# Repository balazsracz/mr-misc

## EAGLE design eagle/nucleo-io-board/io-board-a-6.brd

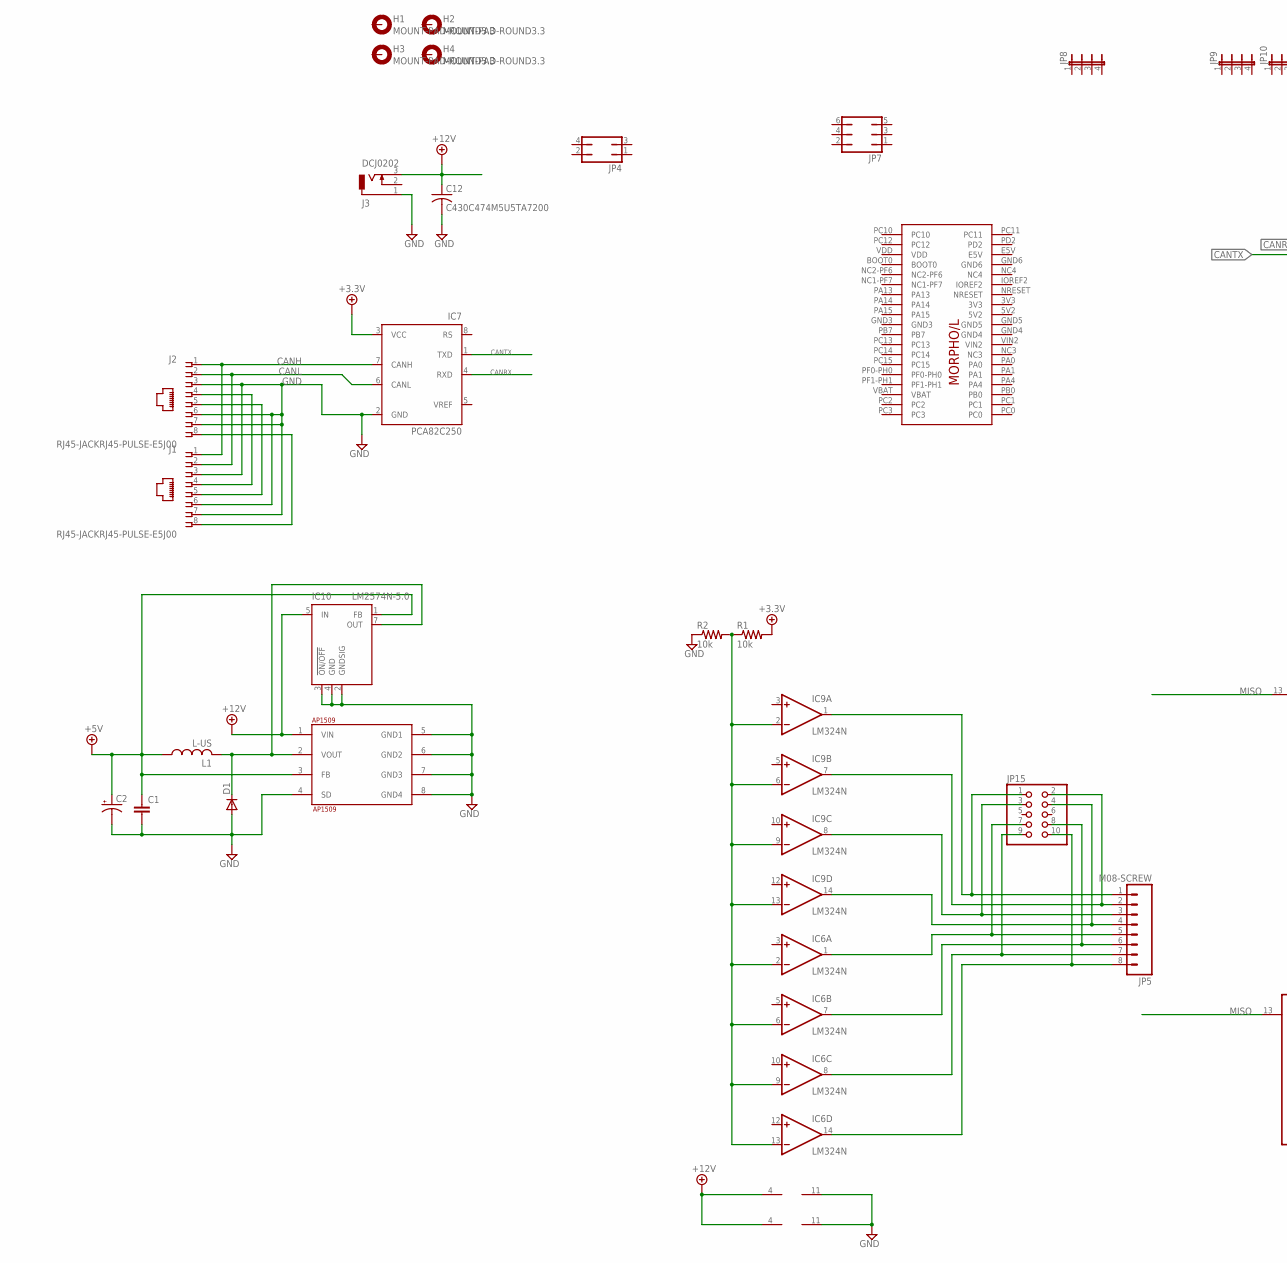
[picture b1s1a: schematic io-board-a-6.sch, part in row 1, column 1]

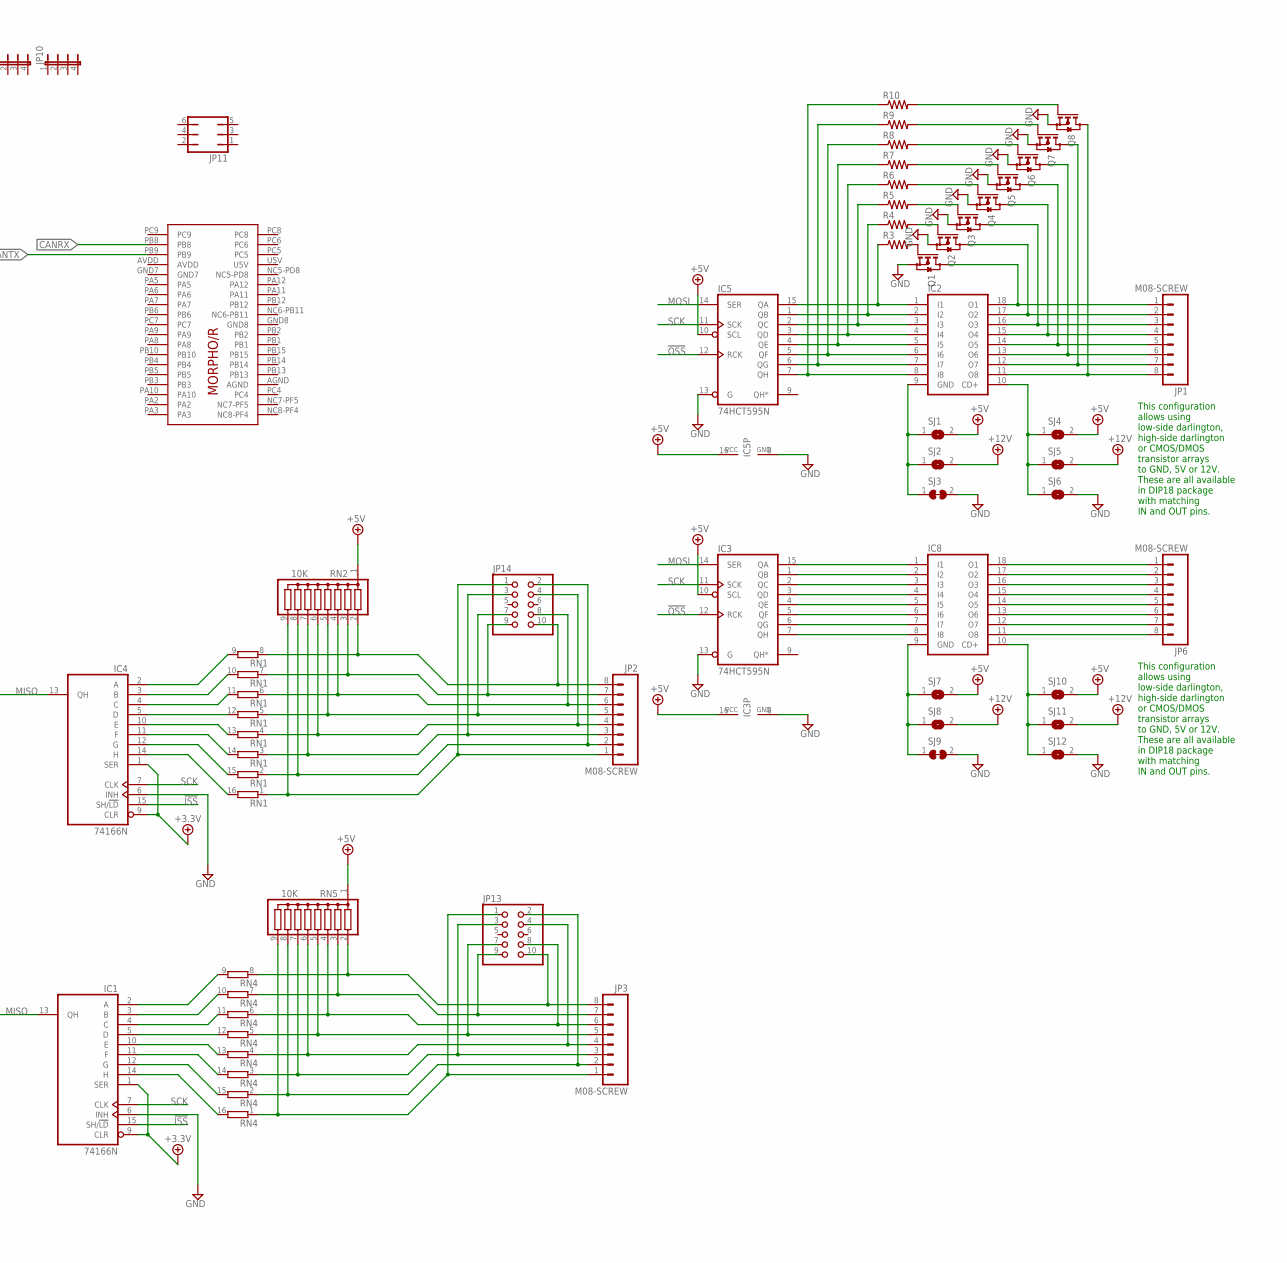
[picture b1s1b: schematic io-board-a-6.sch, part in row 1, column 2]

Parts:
+12V: 9-15V; POWER_USAGE
AP1509: AP1509; SO-08
C1: C-EUC1206; C1206
C2: CPOL-USE2.5-5; E2,5-5
C12: C430C474M5U5TA7200; C075-032X103
D1: DIODE-DO41-7.6; DO41-7.6
H1, H2, H3, H4: MOUNT-PAD-ROUND3.3; 3,3-PAD
IC1, IC4: 74166N; DIL16
IC2, IC8: ULN2803A; DIL18-THIN
IC3, IC5: 74HCT595N; DIL16
IC6, IC9: LM324N; DIL14
IC7: PCA82C250; DIL08
IC10: LM2574N-5.0; DIL08
J1, J2: RJ45-JACKRJ45-PULSE-E5J00; RJ45-PULSE-E5J88
J3: DCJ0202
JP1, JP2, JP3, JP5, JP6: M08-SCREW; 1X08_TERMINAL
JP4: JP2Q
JP7, JP11: JP3Q
JP8, JP9, JP10: JP4-FLAT; JP4F
JP13, JP14, JP15: PINHD-2X5CN; CON10M
L1: L-US; L5-8,5
Q1, Q2, Q3, Q4, Q5, Q6, Q7, Q8: BSS123; SOT23
R1, R2: 10k; R1206
R3, R4, R5, R6, R7, R8, R9, R10: R-US_R0603; R0603
RN1, RN4: 8R-P; DIL16
RN2, RN5: 10K; SIL9
SJ1, SJ2, SJ4, SJ5, SJ6, SJ7, SJ8, SJ10, SJ11, SJ12: SJ; SJ-RND
SJ3, SJ9: SJ-C; SJW-C
U$1: NUCLEO_64_GENERIC; NUCLEO_BRD_BASE64

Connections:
3V3: U$1.3V3
5V2: U$1.5V2
!ISS: IC1.15 (SH/!LD), IC4.15 (SH/!LD)
!OSS: IC3.12 (RCK), IC5.12 (RCK)
+3.3V: IC1.1 (SER), IC1.9 (CLR), IC4.1 (SER), IC4.9 (CLR), IC7.3 (VCC), R1.2
+5V: AP1509.3 (FB), C1.1, C2.+, IC3.10 (SCL), IC3.16 (VCC), IC5.10 (SCL), IC5.16 (VCC), IC10.1 (FB), L1.1, RN2.1, RN5.1, SJ1.2, SJ4.2, SJ7.2, SJ10.2
+12V: AP1509.1 (VIN), C12.1, IC6.4 (V+), IC9.4 (V+), IC10.5 (IN), J3.3, SJ2.2, SJ5.2, SJ8.2, SJ11.2
AGND: U$1.AGND
AVDD: U$1.AVDD
CANH: IC7.7 (CANH), J1.1, J2.1
CANL: IC7.6 (CANL), J1.2, J2.2
CANRX: IC7.4 (RXD), U$1.PB8
CANTX: IC7.1 (TXD), U$1.PB9
E5V: U$1.E5V
GND: AP1509.4 (SD), AP1509.5 (GND1), AP1509.6 (GND2), AP1509.7 (GND3), AP1509.8 (GND4), C1.2, C2.-, C12.2, D1.A, IC1.6 (INH), IC1.8 (GND), IC3.8 (GND), IC3.13 (G), IC4.6 (INH), IC4.8 (GND), IC5.8 (GND), IC5.13 (G), IC6.11 (V-), IC7.2 (GND), IC9.11 (V-), IC10.2 (GNDSIG), IC10.3 (!ON/OFF), IC10.4 (GND), J1.3, J1.6, J1.7, J2.3, J2.6, J2.7, J3.1, Q1.2 (S), Q2.2 (S), Q3.2 (S), Q4.2 (S), Q5.2 (S), Q6.2 (S), Q7.2 (S), Q8.2 (S), R2.1, SJ3.2, SJ6.2, SJ9.2, SJ12.2
GND3: U$1.GND3
GND4: U$1.GND4
GND5: U$1.GND5
GND6: U$1.GND6
GND7: U$1.GND7
GND8: U$1.GND8
MISO: IC1.13 (QH), IC4.13 (QH)
MOSI: IC3.14 (SER), IC5.14 (SER)
unnamed: IC2.1 (I1), IC5.15 (QA), R3.1
unnamed: IC2.18 (O1), JP1.1, Q1.3 (D)
unnamed: IC2.2 (I2), IC5.1 (QB), R4.1
unnamed: J1.4, J2.4
unnamed: J1.5, J2.5
unnamed: JP3.8, JP13.10, RN4.8 (1), RN5.2
unnamed: IC2.17 (O2), JP1.2, Q2.3 (D)
unnamed: IC2.3 (I3), IC5.2 (QC), R5.1
unnamed: IC2.16 (O3), JP1.3, Q3.3 (D)
unnamed: IC2.4 (I4), IC5.3 (QD), R6.1
unnamed: IC2.15 (O4), JP1.4, Q4.3 (D)
unnamed: IC2.5 (I5), IC5.4 (QE), R7.1
unnamed: IC2.14 (O5), JP1.5, Q5.3 (D)
unnamed: JP3.7, JP13.9, RN4.7 (1), RN5.3
unnamed: JP3.6, JP13.8, RN4.6 (1), RN5.4
unnamed: Q4.1 (G), R6.2
unnamed: IC2.6 (I6), IC5.5 (QF), R8.1
unnamed: IC2.13 (O6), JP1.6, Q6.3 (D)
unnamed: JP3.4, JP13.4, RN4.4 (1), RN5.6
unnamed: JP3.3, JP13.3, RN4.3 (1), RN5.7
unnamed: JP2.6, JP14.8, RN1.6 (1), RN2.4
unnamed: JP3.1, JP13.1, RN4.1, RN5.9
unnamed: IC1.2 (A), RN4.9 (2)
unnamed: IC1.3 (B), RN4.10 (2)
unnamed: JP2.8, JP14.10, RN1.8 (1), RN2.2
unnamed: JP2.7, JP14.9, RN1.7 (1), RN2.3
unnamed: Q5.1 (G), R7.2
unnamed: JP2.5, JP14.7, RN1.5 (1), RN2.5
unnamed: IC1.4 (C), RN4.11 (2)
unnamed: IC1.5 (D), RN4.12 (2)
unnamed: IC1.10 (E), RN4.13 (2)
unnamed: IC1.11 (F), RN4.14 (2)
unnamed: JP2.4, JP14.4, RN1.4 (1), RN2.6
unnamed: JP2.3, JP14.3, RN1.3 (1), RN2.7
unnamed: JP2.2, JP14.2, RN1.2 (1), RN2.8
unnamed: JP2.1, JP14.1, RN1.1, RN2.9
unnamed: IC1.12 (G), RN4.15 (2)
unnamed: IC1.14 (H), RN4.16 (2)
unnamed: IC2.7 (I7), IC5.6 (QG), R9.1
unnamed: IC2.12 (O7), JP1.7, Q7.3 (D)
unnamed: IC2.8 (I8), IC5.7 (QH), R10.1
unnamed: IC2.11 (O8), JP1.8, Q8.3 (D)
unnamed: Q6.1 (G), R8.2
unnamed: IC4.2 (A), RN1.9 (2)
unnamed: IC6.2 (-IN), IC6.6 (-IN), IC6.9 (-IN), IC6.13 (-IN), IC9.2 (-IN), IC9.6 (-IN), IC9.9 (-IN), IC9.13 (-IN), R1.1, R2.2
unnamed: IC9.7 (OUT), JP5.2, JP15.2
unnamed: IC4.3 (B), RN1.10 (2)
unnamed: IC4.4 (C), RN1.11 (2)
unnamed: IC4.5 (D), RN1.12 (2)
unnamed: IC4.10 (E), RN1.13 (2)
unnamed: IC4.11 (F), RN1.14 (2)
unnamed: IC4.12 (G), RN1.15 (2)
unnamed: IC4.14 (H), RN1.16 (2)
unnamed: IC2.9 (GND), SJ1.1, SJ2.1, SJ3.1
unnamed: IC2.10 (CD+), SJ4.1, SJ5.1, SJ6.1
unnamed: IC3.15 (QA), IC8.1 (I1)
unnamed: IC8.18 (O1), JP6.1
unnamed: IC3.1 (QB), IC8.2 (I2)
unnamed: IC8.17 (O2), JP6.2
unnamed: IC6.7 (OUT), JP5.6, JP15.8
unnamed: IC3.2 (QC), IC8.3 (I3)
unnamed: IC8.16 (O3), JP6.3
unnamed: IC6.14 (OUT), JP5.8, JP15.10
unnamed: IC6.1 (OUT), JP5.5, JP15.7
unnamed: Q7.1 (G), R9.2
unnamed: IC3.3 (QD), IC8.4 (I4)
unnamed: IC8.15 (O4), JP6.4
unnamed: IC3.4 (QE), IC8.5 (I5)
unnamed: IC8.14 (O5), JP6.5
unnamed: IC3.5 (QF), IC8.6 (I6)
unnamed: IC8.13 (O6), JP6.6
unnamed: IC3.6 (QG), IC8.7 (I7)
unnamed: IC8.12 (O7), JP6.7
unnamed: IC3.7 (QH), IC8.8 (I8)
unnamed: IC8.11 (O8), JP6.8
unnamed: IC8.9 (GND), SJ7.1, SJ8.1, SJ9.1
unnamed: IC8.10 (CD+), SJ10.1, SJ11.1, SJ12.1
unnamed: Q1.1 (G), R3.2
unnamed: Q2.1 (G), R4.2
unnamed: IC9.14 (OUT), JP5.4, JP15.4
unnamed: IC9.1 (OUT), JP5.1, JP15.1
unnamed: IC9.8 (OUT), JP5.3, JP15.3
unnamed: JP3.5, JP13.7, RN4.5 (1), RN5.5
unnamed: JP3.2, JP13.2, RN4.2 (1), RN5.8
unnamed: Q8.1 (G), R10.2
unnamed: Q3.1 (G), R5.2
unnamed: IC6.8 (OUT), JP5.7, JP15.9
PWR_POS: J1.8, J2.8
SCK: IC1.7 (CLK), IC3.11 (SCK), IC4.7 (CLK), IC5.11 (SCK)
SW: AP1509.2 (VOUT), D1.C, IC10.7 (OUT), L1.2
U5V: U$1.U5V
VBAT: U$1.VBAT
VCC: IC1.16 (VCC), IC4.16 (VCC)
VDD: U$1.VDD
VIN2: U$1.VIN2

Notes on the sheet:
This configuration allows using low-side darlington, high-side darlington or CMOS/DMOS transistor arrays to GND, 5V or 12V. These are all available in DIP18 package with matching IN and OUT pins.

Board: 2 copper layers, 73 parts (14 on the bottom side), 103 nets, no tracks yet.
